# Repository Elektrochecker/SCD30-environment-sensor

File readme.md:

compile for AVR
```
./avr-compile.sh main.c
```

flash with avrdude
```
avrdude -v -c stk500 -p m328p -P /dev/ttyACM0 -U flash:w:build/main.hex:i
```

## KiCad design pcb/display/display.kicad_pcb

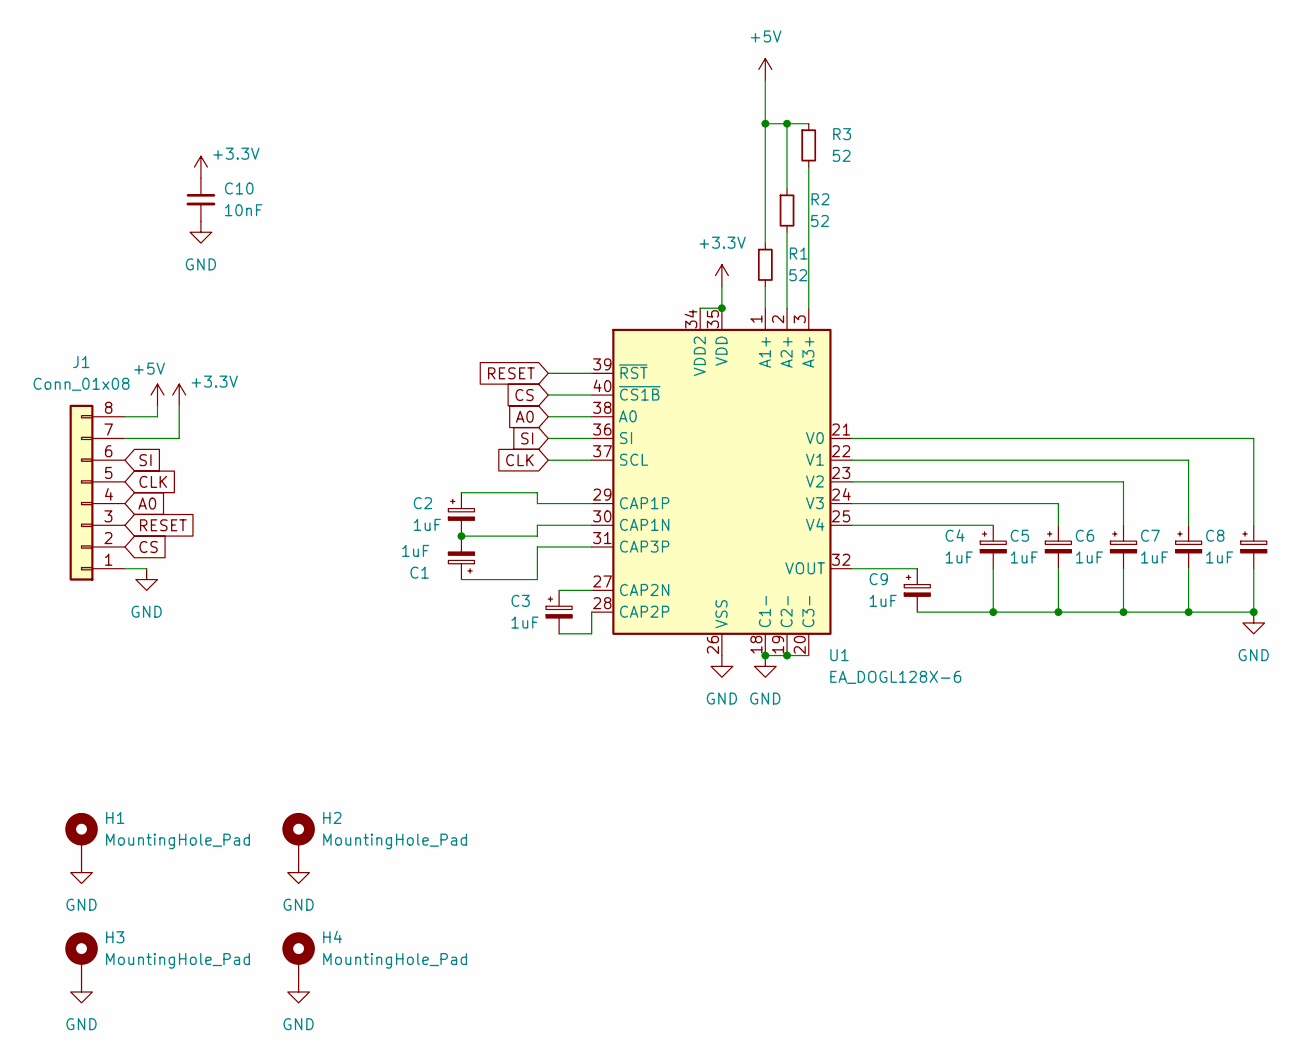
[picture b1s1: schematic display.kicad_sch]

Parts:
C1, C2, C3, C4, C5, C6, C7, C8, C9: 1uF; CP_Radial_D5.0mm_P2.50mm
C10: 10nF; C_Disc_D3.8mm_W2.6mm_P2.50mm
H1, H2, H3, H4: MountingHole_Pad; MountingHole_3.2mm_M3_DIN965_Pad
J1: Conn_01x08; PinHeader_1x08_P2.54mm_Vertical
R1, R2, R3: 52; R_Axial_DIN0207_L6.3mm_D2.5mm_P10.16mm_Horizontal
U1: EA_DOGL128X-6; EA_DOGL128-6

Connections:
+3.3V: C10.1, J1.7, U1.34 (VDD2), U1.35 (VDD)
+5V: J1.8, R1.1, R2.1, R3.1
A0: J1.4, U1.38 (A0)
CLK: J1.5, U1.37 (SCL)
CS: J1.2, U1.40 (~CS1B)
GND: C4.2, C5.2, C6.2, C7.2, C8.2, C9.2, C10.2, H1.1, H2.1, H3.1, H4.1, J1.1, U1.18 (C1-), U1.19 (C2-), U1.20 (C3-), U1.26 (VSS), U1.33 (VSS)
unnamed: R1.2, U1.1 (A1+)
unnamed: R2.2, U1.2 (A2+)
unnamed: R3.2, U1.3 (A3+)
unnamed: C1.2, C2.2, U1.30 (CAP1N)
unnamed: C2.1, U1.29 (CAP1P)
unnamed: C3.1, U1.27 (CAP2N)
unnamed: C3.2, U1.28 (CAP2P)
unnamed: C1.1, U1.31 (CAP3P)
unnamed: C8.1, U1.21 (V0)
unnamed: C7.1, U1.22 (V1)
unnamed: C6.1, U1.23 (V2)
unnamed: C5.1, U1.24 (V3)
unnamed: C4.1, U1.25 (V4)
unnamed: C9.1, U1.32 (VOUT)
RESET: J1.3, U1.39 (~RST)
SI: J1.6, U1.36 (SI)

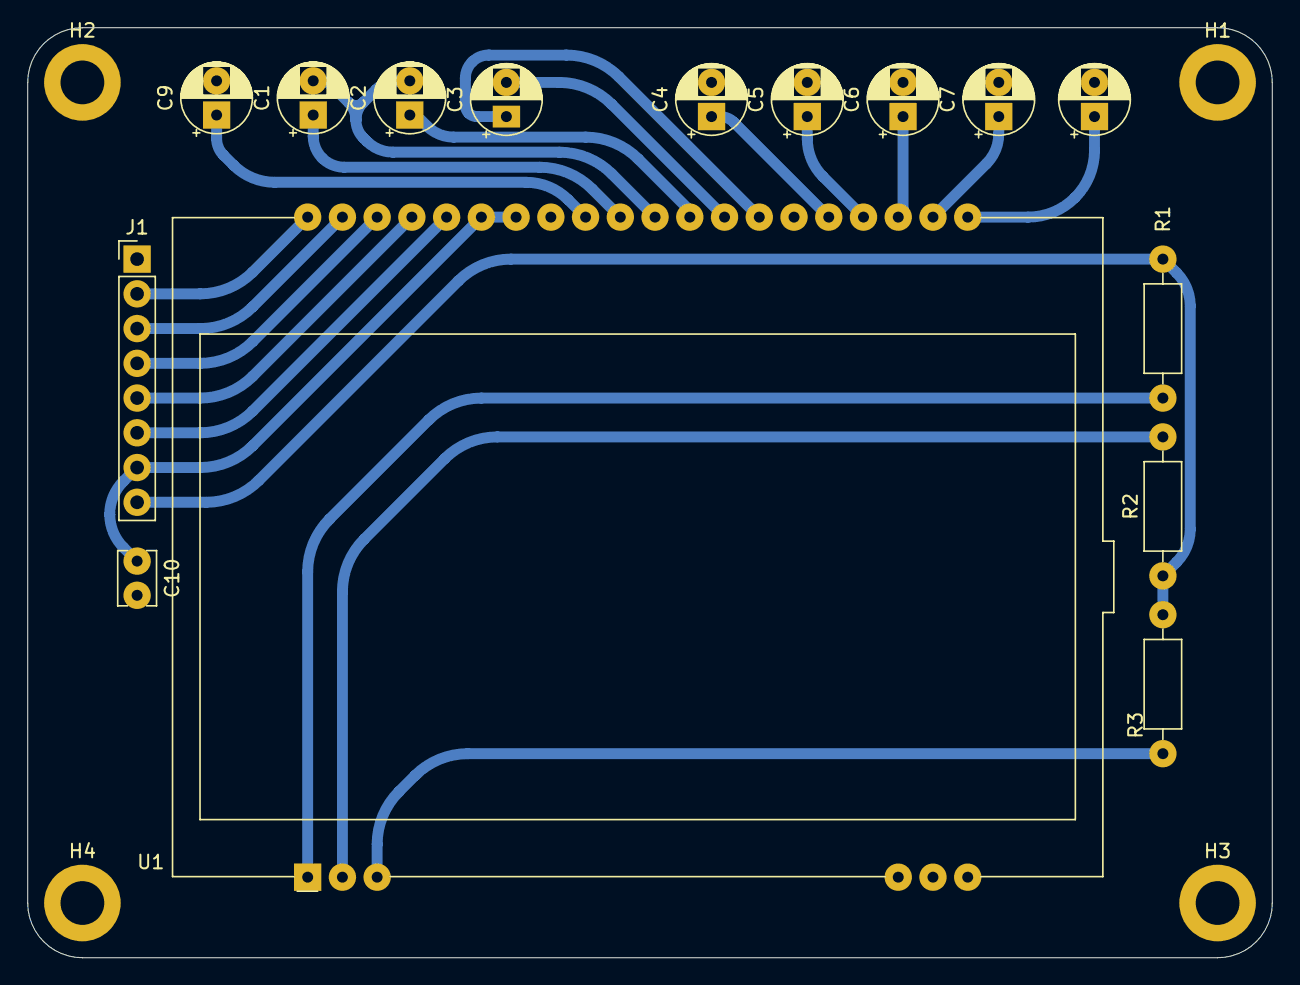
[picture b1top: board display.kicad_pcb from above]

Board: 2 copper layers, 91.0 x 68.0 mm, 19 parts (0 on the bottom side), 22 nets.

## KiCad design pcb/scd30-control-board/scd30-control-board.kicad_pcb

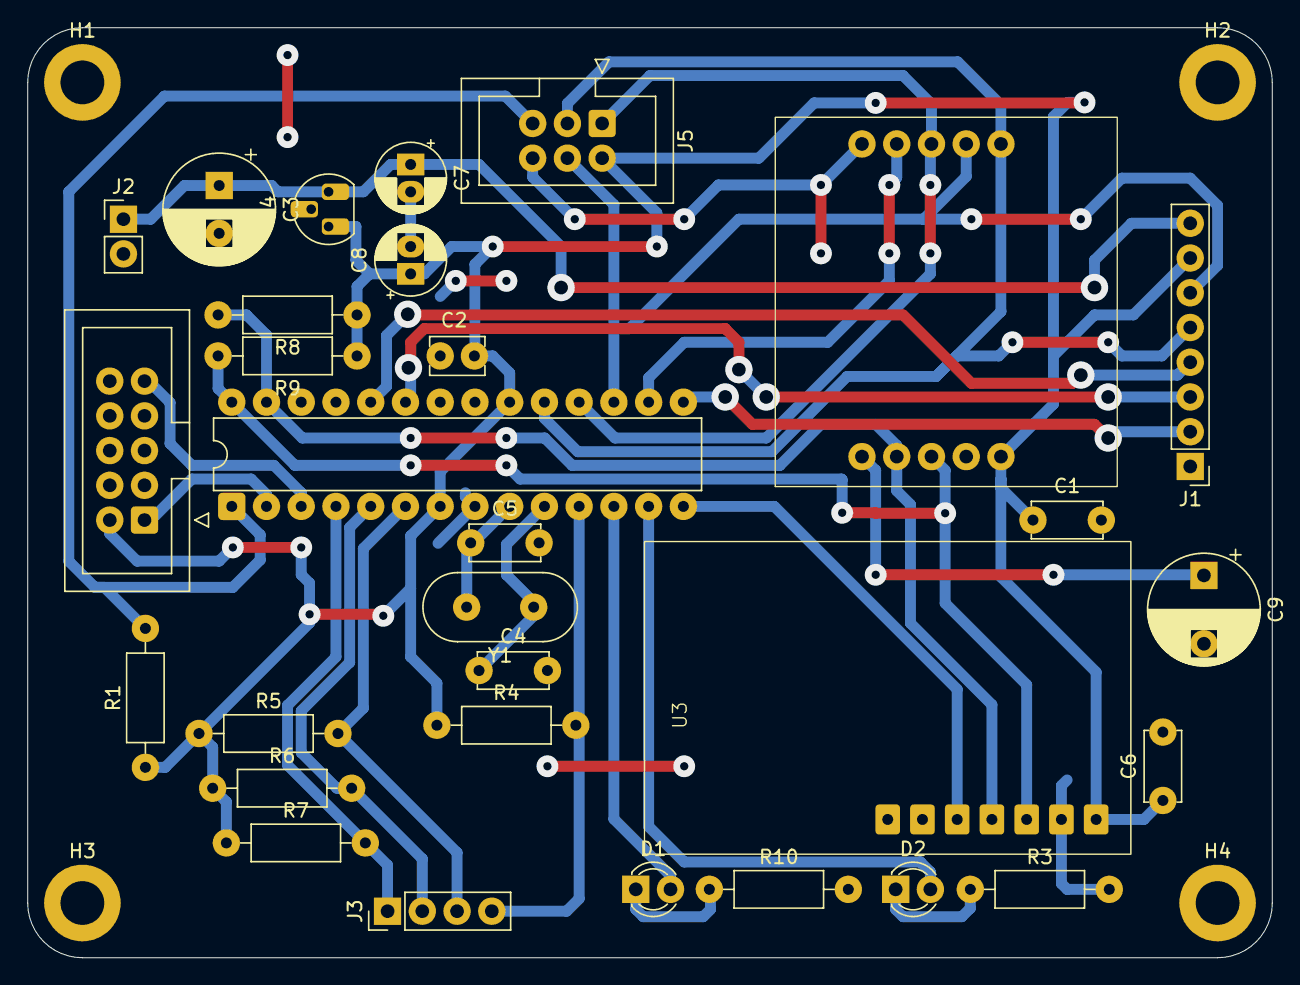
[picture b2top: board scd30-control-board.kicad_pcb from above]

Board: 2 copper layers, 91.0 x 68.0 mm, 34 parts (0 on the bottom side), 27 nets.

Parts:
C1, C6: 100nF; C_Disc_D5.0mm_W2.5mm_P5.00mm
C2: 10nF; C_Disc_D3.8mm_W2.6mm_P2.50mm
C3: 330uF; CP_Radial_D8.0mm_P3.50mm
C4, C5: 22pF; C_Disc_D5.0mm_W2.5mm_P5.00mm
C7, C8: 1uF; CP_Radial_D5.0mm_P2.00mm
C9: C_Polarized; CP_Radial_D8.0mm_P5.00mm
D1, D2: LED_Small; LED_D3.0mm
H1, H2, H3, H4: MountingHole_Pad; MountingHole_3.2mm_M3_DIN965_Pad
J1: Conn_01x08; PinHeader_1x08_P2.54mm_Vertical
J2: Conn_01x02; PinHeader_1x02_P2.54mm_Vertical
J3: Conn_01x04; PinHeader_1x04_P2.54mm_Vertical
J4: UART; IDC-Header_2x05_P2.54mm_Vertical
J5: ISP; IDC-Header_2x03_P2.54mm_Vertical
R1, R4, R5, R6, R7: 100k; R_Axial_DIN0207_L6.3mm_D2.5mm_P10.16mm_Horizontal
R3, R8, R9, R10: 1k; R_Axial_DIN0207_L6.3mm_D2.5mm_P10.16mm_Horizontal
U1: clock&memory_module
U2: ATmega328P-P; DIP-28_W7.62mm
U3: SCD30
U4: LP2950-3.3_TO92; TO-92_HandSolder
Y1: Crystal_Small; Crystal_HC18-U_Vertical

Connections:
+3.3V: C1.1, C2.1, C6.1, C8.1, J1.7, J4.2, J5.2, R1.1, R4.1, R5.1, R6.1, R7.1, R8.1, R9.1, U1.5 (3V3), U2.7 (VCC), U2.20 (AVCC), U3.1 (VIN), U4.1 (VO)
+5V: C3.1, C7.1, J1.8, J2.1, U4.3 (VI)
/DISPLAY_A0: J1.4, U2.24 (PC1)
/DISPLAY_RESET: J1.3, U2.23 (PC0)
/I2C_SCL: R9.2, U1.3 (SCL), U2.28 (PC5), U3.3 (SCL)
/I2C_SDA: R8.2, U1.2 (SDA), U2.27 (PC4), U3.4 (SDA)
/RESET: J5.5, R1.2, U2.1 (~RESET/PC6)
/SENSOR_RDY: U2.14 (PB0), U3.5 (RDY)
/SPI_CLK: J1.5, J5.3, U1.6 (CLK), U2.19 (PB5)
/SPI_CS_FLASHMEM: U1.9 (CS), U2.16 (PB2)
/SPI_CS_LCD: J1.2, U2.15 (PB1)
/SPI_MISO: J5.1, U1.8 (MISO), U2.18 (PB4)
/SPI_MOSI: J1.6, J5.4, U1.7 (MOSI), U2.17 (PB3)
/UART_RX: J4.1, U2.2 (PD0)
/UART_TX: J4.9, U2.3 (PD1)
GND: C1.2, C2.2, C3.2, C4.2, C5.2, C6.2, C7.2, C8.2, C9.2, H1.1, H2.1, H3.1, H4.1, J1.1, J2.2, J4.10, J5.6, R3.2, R10.2, U1.10 (GND), U2.8 (GND), U2.22 (GND), U3.2 (GND), U3.7 (SEL), U4.2 (GND)
unnamed: D1.2 (A), U2.12 (PD6)
unnamed: D1.1 (K), R10.1
unnamed: D2.2 (A), U2.13 (PD7)
unnamed: D2.1 (K), R3.1
unnamed: J3.1, R7.2, U2.4 (PD2)
unnamed: J3.2, R6.2, U2.5 (PD3)
unnamed: J3.3, R5.2, U2.6 (PD4)
unnamed: J3.4, R4.2, U2.11 (PD5)
unnamed: C9.1, U1.1 (VBACKUP)
unnamed: C5.1, U2.9 (XTAL1/PB6), Y1.2
unnamed: C4.1, U2.10 (XTAL2/PB7), Y1.1

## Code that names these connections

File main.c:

#include "config.h"
#define CPU_CLOCK_FREQUENCY F_CPU

#include <avr/io.h>
#include <util/delay.h>

#include "clock.h"
#include "display.h"
#include "scene.h"
#include "sensor.h"
#include "spi.h"
#include "storage.h"
#include "twi.h"
#include "uart.h"

// IO CONNECTIVITY

// PB0 -> sensor RDY
// PB1 -> CS display
// PB2 -> CS flash chip
// PB3 -> MOSI
// PB4 -> MISO
// PB5 -> CLK
// PC0 -> display reset
// PC1 -> display A0
// PC4 -> TWI SDA
// PC5 -> TWI SCL
// PD2 .. PD5 -> user buttons (4)
// PD6 -> TWI error / Flash storage write LED (red)
// PD7 -> program LED (blue)

// uncomment to set the datetime when flashing.
// must flash a second time with this option turned off again
// #define DO_SET_DATETIME

#define MAIN_LOOP_DELAY 200U
#define DATA_SAVE_INTERVAL 60U // seconds
#define DATA_SAVE_LOOP_COUNT DATA_SAVE_INTERVAL * 1000U / MAIN_LOOP_DELAY
uint16_t data_save_counter = 0;

int main(void) {

  SPI_init();
  TWI_init();
  UART_init();

  _delay_ms(100);

  SENSOR_init();
  CLOCK_init();
  DISPLAY_init();
  DISPLAY_clear();
  STORAGE_init();

  DDRD |= (1 << PD7);
  // PORTD |= (1 << PD7);

  _delay_ms(500);

  // STORAGE_print_debug_information();

  // STORAGE_block_erase_32k(0);

  // scan the flash chip for the last written datapoint
  DISPLAY_set_pos(0, 0);
  DISPLAY_write("Scanning storage...");
  STORAGE_current_location = STORAGE_scan_location();

  // dump current database on startup
  DISPLAY_set_pos(1, 0);
  DISPLAY_write("Dumping data...");
  STORAGE_dump_datapoints_to_uart();

  // UART_send_string("\r\nstorage location ");
  // UART_send_number_hex_32(STORAGE_current_location);
  //
  // STORAGE_print_page_data(STORAGE_current_location*16-256);
  // STORAGE_print_page_data(STORAGE_current_location*16);
  // STORAGE_print_page_data(STORAGE_current_location*16+256);

  // set date & time
#ifdef DO_SET_DATETIME
  DATETIME time = {.seconds = 0, .minutes = 32, .hours = 12, .weekday = 1, .day = 9, .month = 6, .year = 2025};
  CLOCK_write_time(time);
#endif

  while (1) {
    SENSOR_reading reading = SENSOR_read_data();
    if (reading.success) {
      SENSOR_last_reading = reading;

      if (data_save_counter >= DATA_SAVE_LOOP_COUNT) {
        STORAGE_save_datapoint(SENSOR_last_reading, CLOCK_read_time());

        data_save_counter = 0;
      }
    }

    SCENE_display_current_scene();
    SCNENE_advance();

    _delay_ms(MAIN_LOOP_DELAY);
    data_save_counter++;
  }

  return 0;
}

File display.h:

#ifndef DISPLAY_H
#define DISPLAY_H

#include "config.h"
#include "spi.h"
#include "display_font.h"
#include <string.h>

#define DISPLAY_CS_PIN PB1
#define DISPLAY_RESET_PIN PC0
#define DISPLAY_A0_PIN PC1

// LCD control bytes
#define DISPLAY_ON 0xaf
#define DISPLAY_OFF 0xae
#define DISPLAY_ADC_NORMAL 0xa0  // col. address 4 - 131
#define DISPLAY_ADC_REVERSE 0xa1 // col. address 0 - 127
#define DISPLAY_COL_START 0      // 0 for ADC_REVERSE, 4 for ADC_NORMAL
#define DISPLAY_DISPLAY_NORMAL 0xa6
#define DISPLAY_DISPLAY_REVERSE 0xa7
#define DISPLAY_ALL_POINTS_OFF 0xa4
#define DISPLAY_ALL_POINTS_ON 0xa5
#define DISPLAY_BIAS_RATIO_ONE_SEVENTH 0xa3
#define DISPLAY_BIAS_RATIO_ONE_NINETH 0xa2
#define DISPLAY_INTERNAL_RESET 0xe2
#define DISPLAY_COM_NORMAL 0xc0  // last 3 bits insignificant
#define DISPLAY_COM_REVERSE 0xc8 // last 3 bits insignificant
#define DISPLAY_STATIC_INDICATOR_OFF 0xac
#define DISPLAY_STATIC_INDICATOR_ON 0xad
#define DISPLAY_STATIC_INDICATOR_FLASHING_ON 0x01  // follows DISPLAY_STATIC_INDICATOR_OFF/ON
#define DISPLAY_STATIC_INDICATOR_FLASHING_OFF 0x00 // follows DISPLAY_STATIC_INDICATOR_OFF/ON
#define DISPLAY_SELECT_BOOSTER_RATIO 0xf8
#define DISPLAY_SELECT_BOOSTER_RATIO_2x3x4x 0x00
#define DISPLAY_SELECT_BOOSTER_RATIO_5x 0x01
#define DISPLAY_NO_OPERATION 0xe3
#define DISPLAY_START_LINE_0 0x40
#define DISPLAY_POWER_CONTROL_BOOSTER_REGULATOR_FOLLOWER 0x2f // 0x28 - 0x2f select internal power supply operating mode
#define DISPLAY_VOLTAGE_REGULATOR_SET 0x27                    // 0x20 - 0x27 select voltage regulator resistor ratio
#define DISPLAY_ELECTRONIC_VOLUME_SET 0x81                    // followed by 0x00 - 0x3f (contrast)

#define DISPLAY_SET_PAGE 0xb0             // 0xb0 - 0xbf (but only pages 0 - 7 used)
#define DISPLAY_SET_COLUMN_MOST_SIG 0x10  // 0x10 - 0x1f
#define DISPLAY_SET_COLUMN_LEAST_SIG 0x00 // 0x00 - 0x0f

// size of display; each row is 8 pixels tall, each column is 1 pixel wide
#define DISPLAY_ROW_SIZE 128
#define DISPLAY_NUMBER_OF_ROWS 8

extern uint8_t frameBuffer[DISPLAY_ROW_SIZE][DISPLAY_NUMBER_OF_ROWS];

extern void DISPLAY_init();
extern void DISPLAY_set_pos(uint8_t row, uint8_t col);
extern void DISPLAY_frame_buffer_set(uint8_t x, uint8_t y, uint8_t state);
extern void DISPLAY_frame_buffer_switch(uint8_t x, uint8_t y);
extern void DISPLAY_clear_frame_buffer();
extern void DISPLAY_show_frame();
extern void DISPLAY_clear();

extern void DISPLAY_hline(uint16_t x, uint16_t y, uint16_t w);
extern void DISPLAY_vline(uint16_t x, uint16_t y, uint16_t h);
extern void DISPLAY_rect_filled(uint16_t x, uint16_t y, uint16_t w, uint16_t h);
extern void DISPLAY_rect_hollow(uint16_t x, uint16_t y, uint16_t w, uint16_t h);
extern void DISPLAY_rect_dashed_intensity(uint16_t x, uint16_t y, uint16_t w, uint16_t h, uint8_t intensity);
extern void DISPLAY_rect_dashed_intensity_angle(uint16_t x, uint16_t y, uint16_t w, uint16_t h, uint8_t intensity, int16_t angle);
extern void DISPLAY_rect_dashed_0(uint16_t x, uint16_t y, uint16_t w, uint16_t h);

extern void DISPLAY_write(char* str);
extern void DISPLAY_write_to_framebuffer(char *str, uint8_t y, uint8_t x);

#endif

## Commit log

2025-04-12 twi send data working
2025-04-12 move F_CPU & part macros to config header. Implement TWI status codes
2025-04-12 add documentation folder
2025-04-15 TWI write mode data streaming
2025-04-18 add uart println
2025-04-18 TWI read routine
2025-04-18 add readme
2025-04-18 sensor data conversion
2025-04-25 add display PCB
2025-05-01 make main PCB
2025-05-04 resize display pcb to match main board
2025-05-07 move twi error messages to flash
2025-05-09 get time from rtc chip
2025-05-09 write clock & implement dates
2025-05-16 rtc bugfixes
2025-05-16 implement spi display
2025-05-16 line & rectangle helper functions for display
2025-05-16 display text using AVR forum font
2025-05-16 show sensor reading on display
2025-05-27 display write text to frame buffer
2025-05-30 Add License
2025-06-07 add flash chip datasheet
2025-06-09 implement flash storage
2025-06-09 serialize date & time for storage
2025-06-10 save measurements to flash storage, dump flash data to UART
2025-06-10 fix serialization of datetime
2025-06-11 improve page dumping
2025-06-11 make storage scanning more robust
2025-06-19 make julia script for plotting data
